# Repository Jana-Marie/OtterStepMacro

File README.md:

# OtterStepMacro

### Issues

 - [ ] Tab spacing needs to be 5.08mm/2" instead of 5mm
 - [ ] Move the Terminal connectors further to the board edge, maybe 0.2mm
 - [x] The two 100nF 0402 caps should be 0603
 - [x] Pullup on TRIG# OtterStepMacro

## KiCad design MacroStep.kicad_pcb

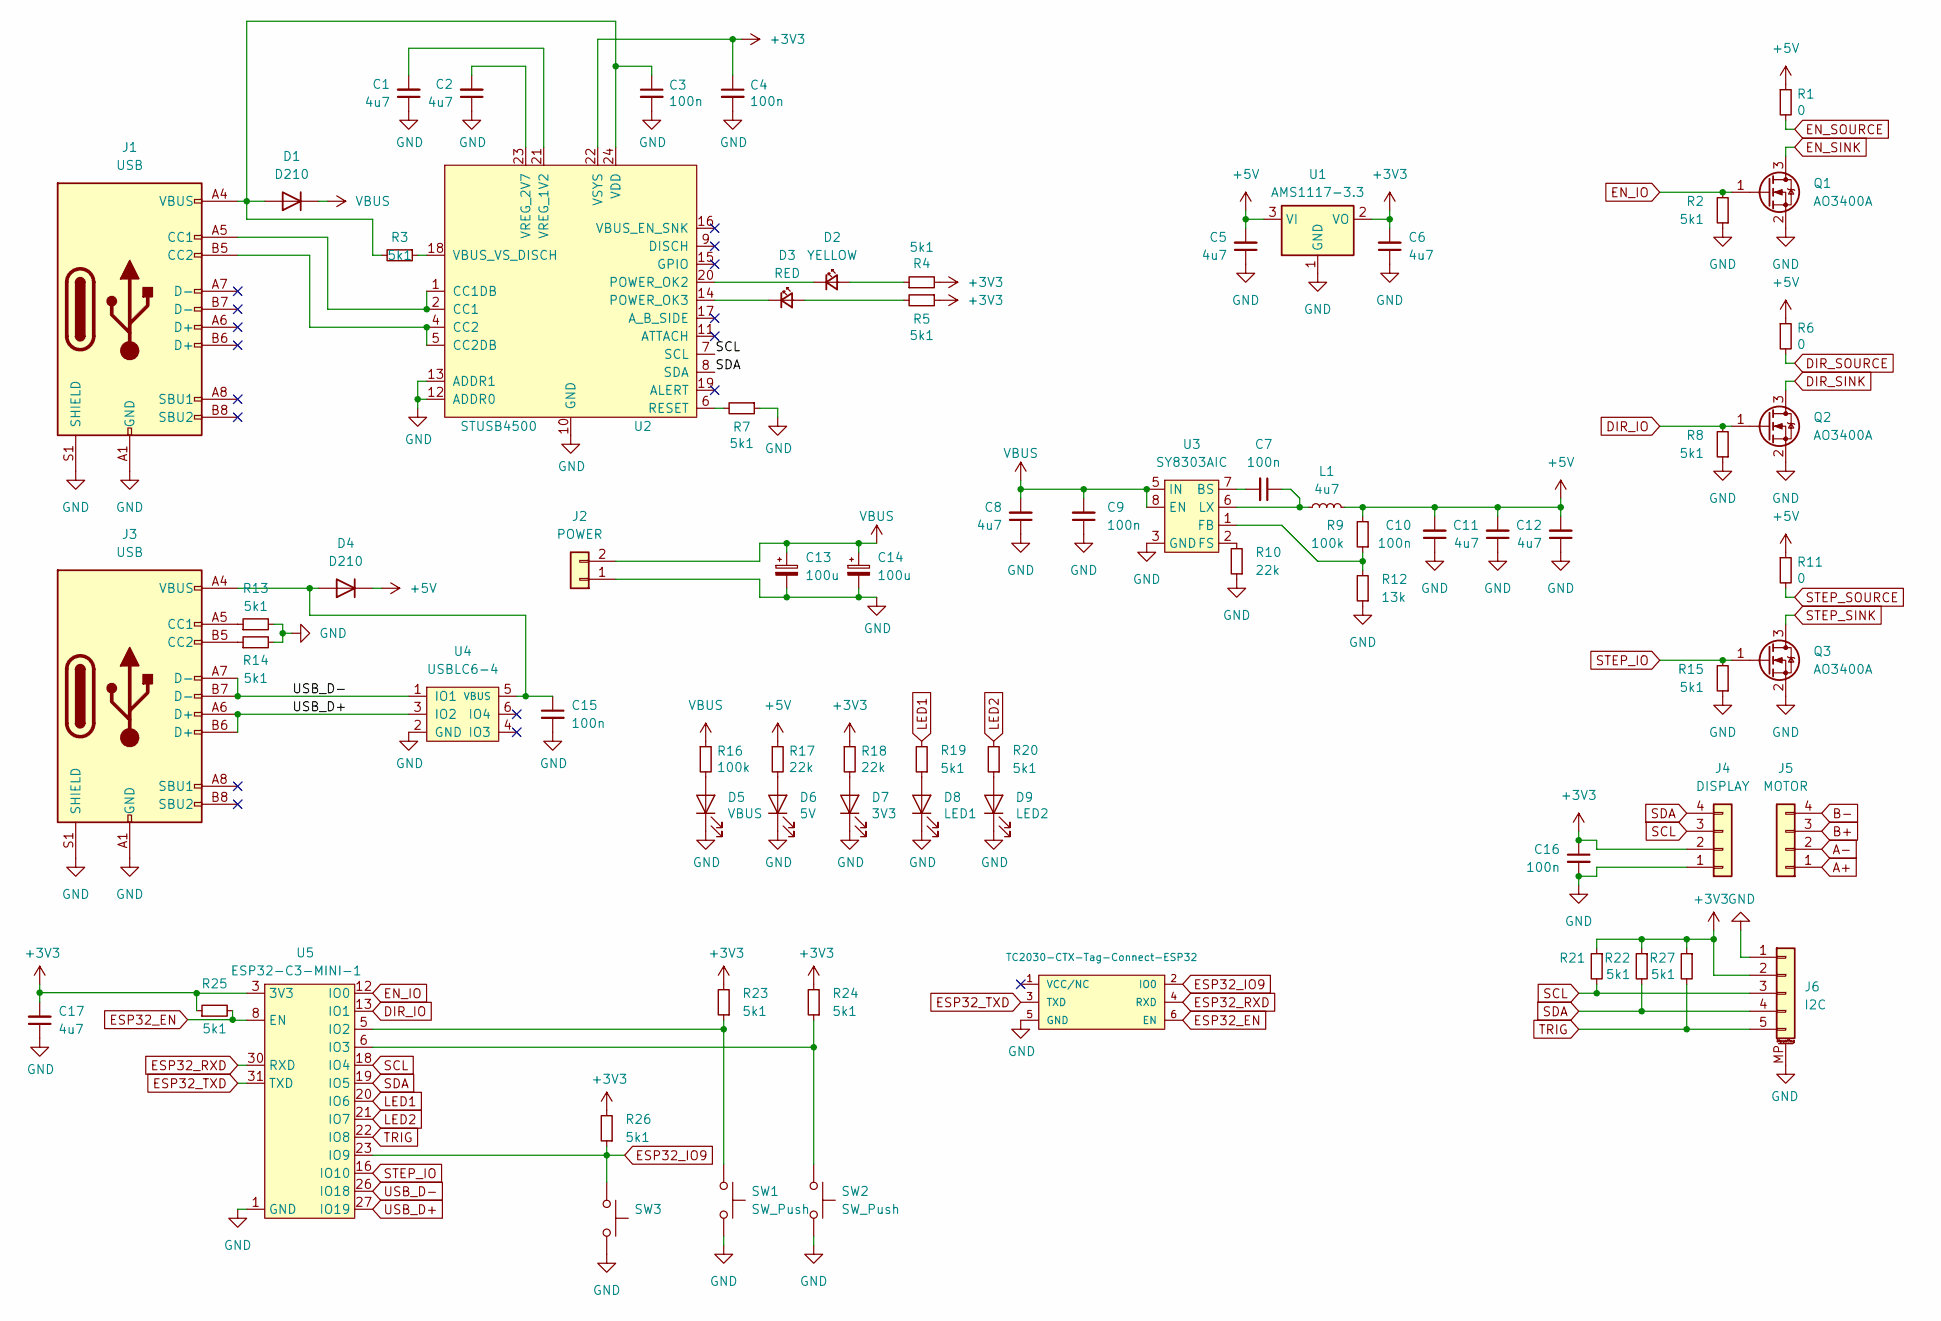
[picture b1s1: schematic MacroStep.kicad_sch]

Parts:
C1, C2, C5, C6, C8, C11, C12, C17: 4u7; C_0805
C3, C4, C7, C9, C10, C15, C16: 100n; C_0603
C13, C14: 100u; CP_Radial_D10.0mm_P5.00mm
D1, D4: D210; D_SMA
D2: YELLOW; LED_0603_1608Metric
D3: RED; LED_0603_1608Metric
D5: VBUS; LED_0603_1608Metric
D6: 5V; LED_0603_1608Metric
D7: 3V3; LED_0603_1608Metric
D8: LED1; LED_0603_1608Metric
D9: LED2; LED_0603_1608Metric
J1, J3: USB; USB-C 16Pin
J2: POWER; PhoenixContact_MC_1,5_2-G-3.5_1x02_P3.50mm_Horizontal
J4: DISPLAY; PinSocket_1x04_P2.54mm_Vertical_center
J5: MOTOR; PhoenixContact_MC_1,5_4-G-3.5_1x04_P3.50mm_Horizontal
J6: I2C; Molex_PicoBlade_53261-0571_1x05-1MP_P1.25mm_Horizontal
L1: 4u7; L_Taiyo-Yuden_MD-4040
P1: TC2030-CTX-Tag-Connect-ESP32; TC2030
Q1, Q2, Q3: AO3400A; SOT-23
R1, R6, R11: 0; R_0603
R2, R3, R4, R5, R7, R8, R13, R14, R15, R19, R20, R21, R22, R23, R24, R25, R26, R27: 5k1; R_0402
R9, R16: 100k; R_0402
R10, R17, R18: 22k; R_0402
R12: 13k; R_0402
SW1, SW2, SW3: SW_Push; SW_SPST_EVQP7C
U1: AMS1117-3.3; SOT-223-3_TabPin2
U2: STUSB4500; QFN-24-1EP_4x4mm_P0.5mm_EP2.7x2.7mm
U3: SY8303AIC; TSOT-23-8
U4: USBLC6-4; SOT-23-6
U5: ESP32-C3-MINI-1

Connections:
+3V3: C4.1, C6.2, C16.1, C17.2, J4.2, J6.2, R4.2, R5.1, R18.1, R21.1, R22.1, R23.2, R24.2, R25.1, R26.2, R27.1, U1.2 (VO), U2.22 (VSYS), U5.3 (3V3)
+5V: C5.2, C10.2, C11.2, C12.2, D4.1 (K), L1.2, R1.1, R6.1, R9.2, R11.1, R17.1, U1.3 (VI)
A+: J5.1
A-: J5.2
B+: J5.3
B-: J5.4
DIR_IO: Q2.1 (G), R8.2, U5.13 (IO1)
DIR_SINK: Q2.3 (D)
DIR_SOURCE: R6.2
EN_IO: Q1.1 (G), R2.2, U5.12 (IO0)
EN_SINK: Q1.3 (D)
EN_SOURCE: R1.2
ESP32_EN: P1.6 (EN), R25.2, U5.8 (EN)
ESP32_IO9: P1.2 (IO0), R26.1, SW3.1, U5.23 (IO9)
ESP32_RXD: P1.4 (RXD), U5.30 (RXD)
ESP32_TXD: P1.3 (TXD), U5.31 (TXD)
GND: C1.1, C2.1, C3.2, C4.2, C5.1, C6.1, C8.1, C9.1, C10.1, C11.1, C12.1, C13.2, C14.2, C15.2, C16.2, C17.1, D5.1 (K), D6.1 (K), D7.1 (K), D8.1 (K), D9.1 (K), J1.A1 (GND), J1.A12 (GND), J1.B1 (GND), J1.B12 (GND), J1.S1 (SHIELD), J2.1, J3.A1 (GND), J3.A12 (GND), J3.B1 (GND), J3.B12 (GND), J3.S1 (SHIELD), J4.1, J6.1, J6.MP (MountPin), P1.5 (GND), Q1.2 (S), Q2.2 (S), Q3.2 (S), R2.1, R7.1, R8.1, R10.1, R12.1, R13.2, R14.2, R15.1, SW1.2, SW2.2, SW3.2, U1.1 (GND), U2.10 (GND), U2.12 (ADDR0), U2.13 (ADDR1), U2.25 (GND), U3.3 (GND), U3.4 (GND), U4.2 (GND), U5.1 (GND), U5.2 (GND), U5.11 (GND), U5.14 (GND), U5.36 (GND), U5.37 (GND), U5.38 (GND), U5.39 (GND), U5.40 (GND), U5.41 (GND), U5.42 (GND), U5.43 (GND), U5.44 (GND), U5.45 (GND), U5.46 (GND), U5.47 (GND), U5.48 (GND), U5.49 (GND), U5.50 (GND), U5.51 (GND), U5.52 (GND), U5.53 (GND)
LED1: R19.2, U5.20 (IO6)
LED2: R20.2, U5.21 (IO7)
unnamed: C3.1, D1.2 (A), J1.A4 (VBUS), J1.A9 (VBUS), J1.B4 (VBUS), J1.B9 (VBUS), R3.2, U2.24 (VDD)
unnamed: D2.2 (A), R4.1
unnamed: D2.1 (K), U2.20 (POWER_OK2)
unnamed: D3.2 (A), R5.2
unnamed: D3.1 (K), U2.14 (POWER_OK3)
unnamed: C15.1, D4.2 (A), J3.A4 (VBUS), J3.A9 (VBUS), J3.B4 (VBUS), J3.B9 (VBUS), U4.5 (VBUS)
unnamed: D5.2 (A), R16.2
unnamed: D6.2 (A), R17.2
unnamed: D7.2 (A), R18.2
unnamed: D8.2 (A), R19.1
unnamed: D9.2 (A), R20.1
unnamed: J1.A5 (CC1), U2.1 (CC1DB), U2.2 (CC1)
unnamed: J1.B5 (CC2), U2.4 (CC2), U2.5 (CC2DB)
unnamed: J3.A5 (CC1), R13.1
unnamed: J3.B5 (CC2), R14.1
unnamed: R7.2, U2.6 (RESET)
unnamed: R3.1, U2.18 (VBUS_VS_DISCH)
unnamed: C1.2, U2.21 (VREG_1V2)
unnamed: C2.2, U2.23 (VREG_2V7)
unnamed: C7.2, U3.7 (BS)
unnamed: R9.1, R12.2, U3.1 (FB)
unnamed: R10.2, U3.2 (FS)
unnamed: C7.1, L1.1, U3.6 (LX)
unnamed: R23.1, SW1.1, U5.5 (IO2)
unnamed: R24.1, SW2.1, U5.6 (IO3)
SCL: J4.3, J6.3, R21.2, U2.7 (SCL), U5.18 (IO4)
SDA: J4.4, J6.4, R22.2, U2.8 (SDA), U5.19 (IO5)
STEP_IO: Q3.1 (G), R15.2, U5.16 (IO10)
STEP_SINK: Q3.3 (D)
STEP_SOURCE: R11.2
TRIG: J6.5, R27.2, U5.22 (IO8)
USB_D+: J3.A6 (D+), J3.B6 (D+), U4.3 (IO2), U5.27 (IO19)
USB_D-: J3.A7 (D-), J3.B7 (D-), U4.1 (IO1), U5.26 (IO18)
VBUS: C8.2, C9.2, C13.1, C14.1, D1.1 (K), J2.2, R16.1, U3.5 (IN), U3.8 (EN)

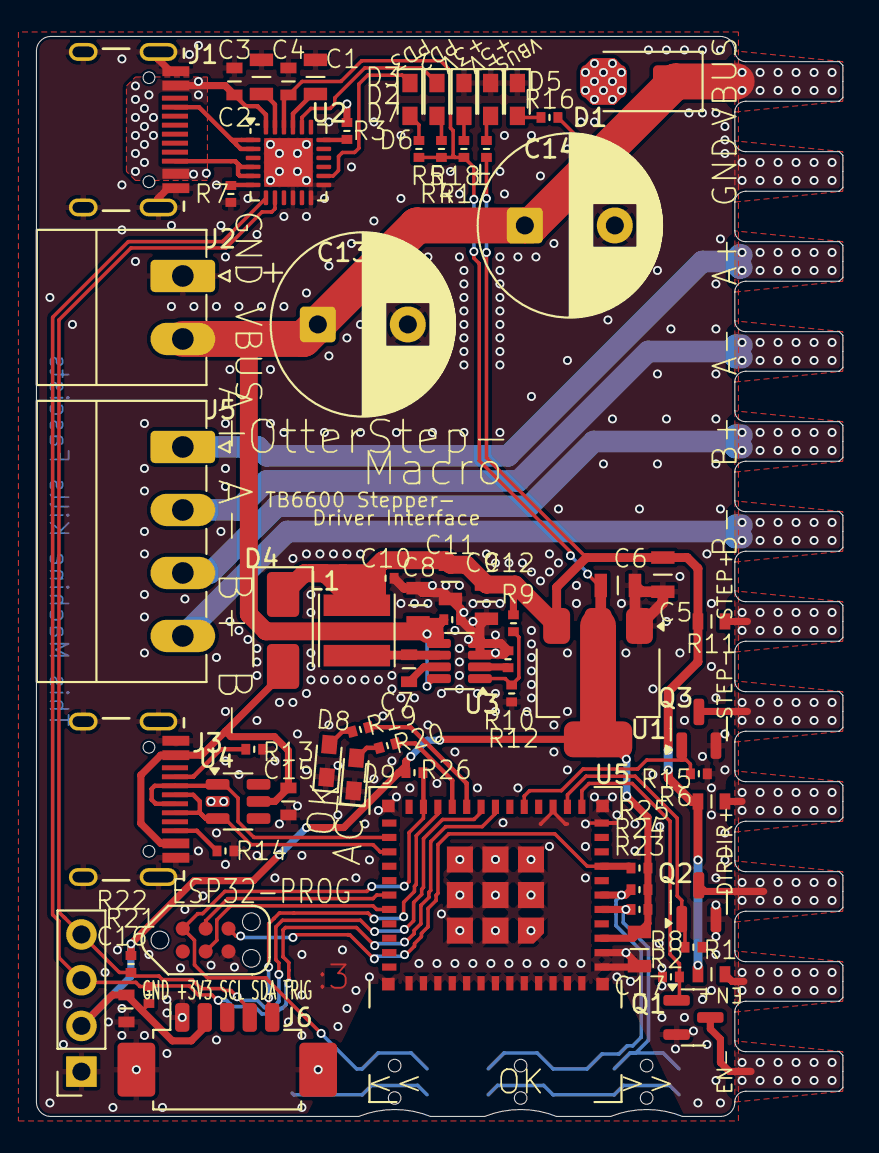
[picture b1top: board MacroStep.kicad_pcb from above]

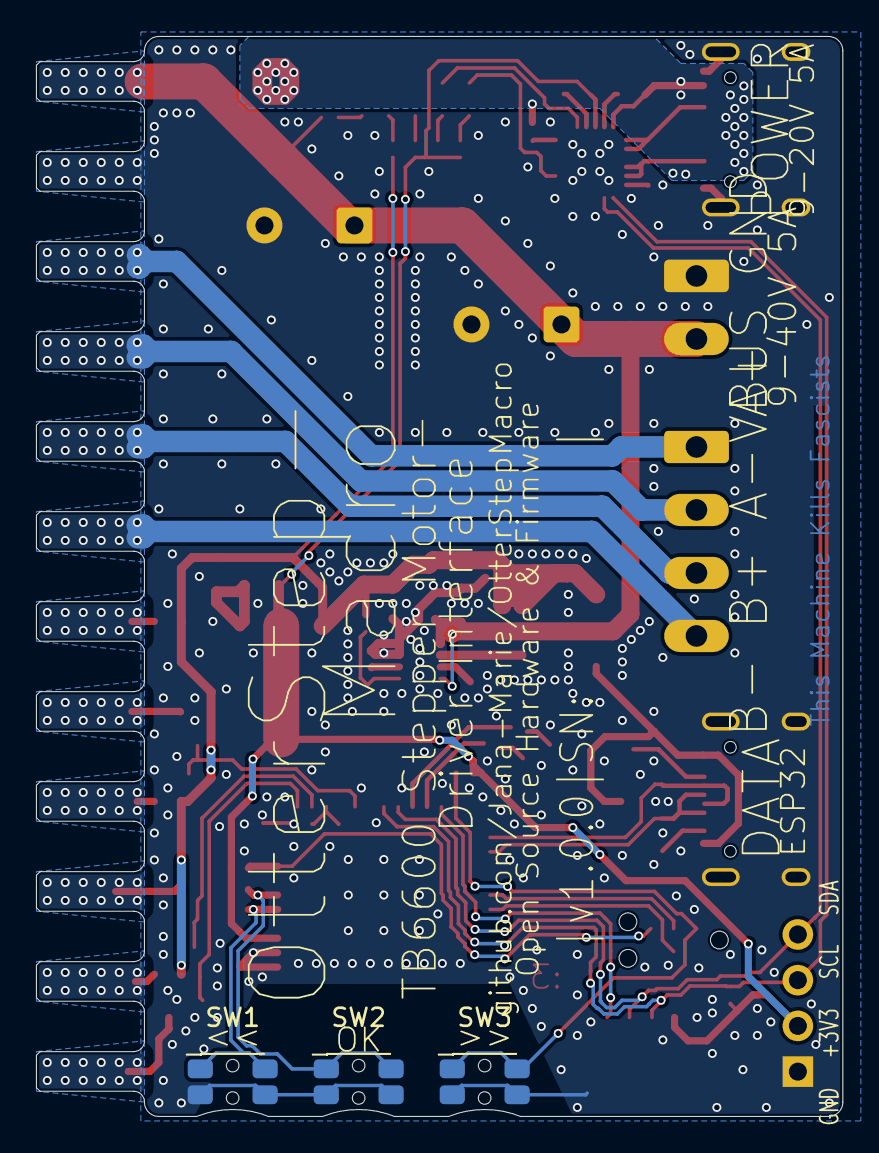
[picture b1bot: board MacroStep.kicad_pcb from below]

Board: 2 copper layers, 44.8 x 60.0 mm, 71 parts (3 on the bottom side), 43 nets.

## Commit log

2025-08-16 added gitignore
2025-08-16 added kicad files
2025-08-16 added bom
2025-08-16 addef preliminary fw
2025-08-17 updated kicad files
2025-08-17 added macro class
2025-08-29 added control class, webcom class, lp class and handler class
2025-08-29 moved handler
2025-08-29 added index.html
2025-08-29 added camera trigger & cleanup
2025-08-30 added X-T4 control
2025-08-30 updated camcontrol
